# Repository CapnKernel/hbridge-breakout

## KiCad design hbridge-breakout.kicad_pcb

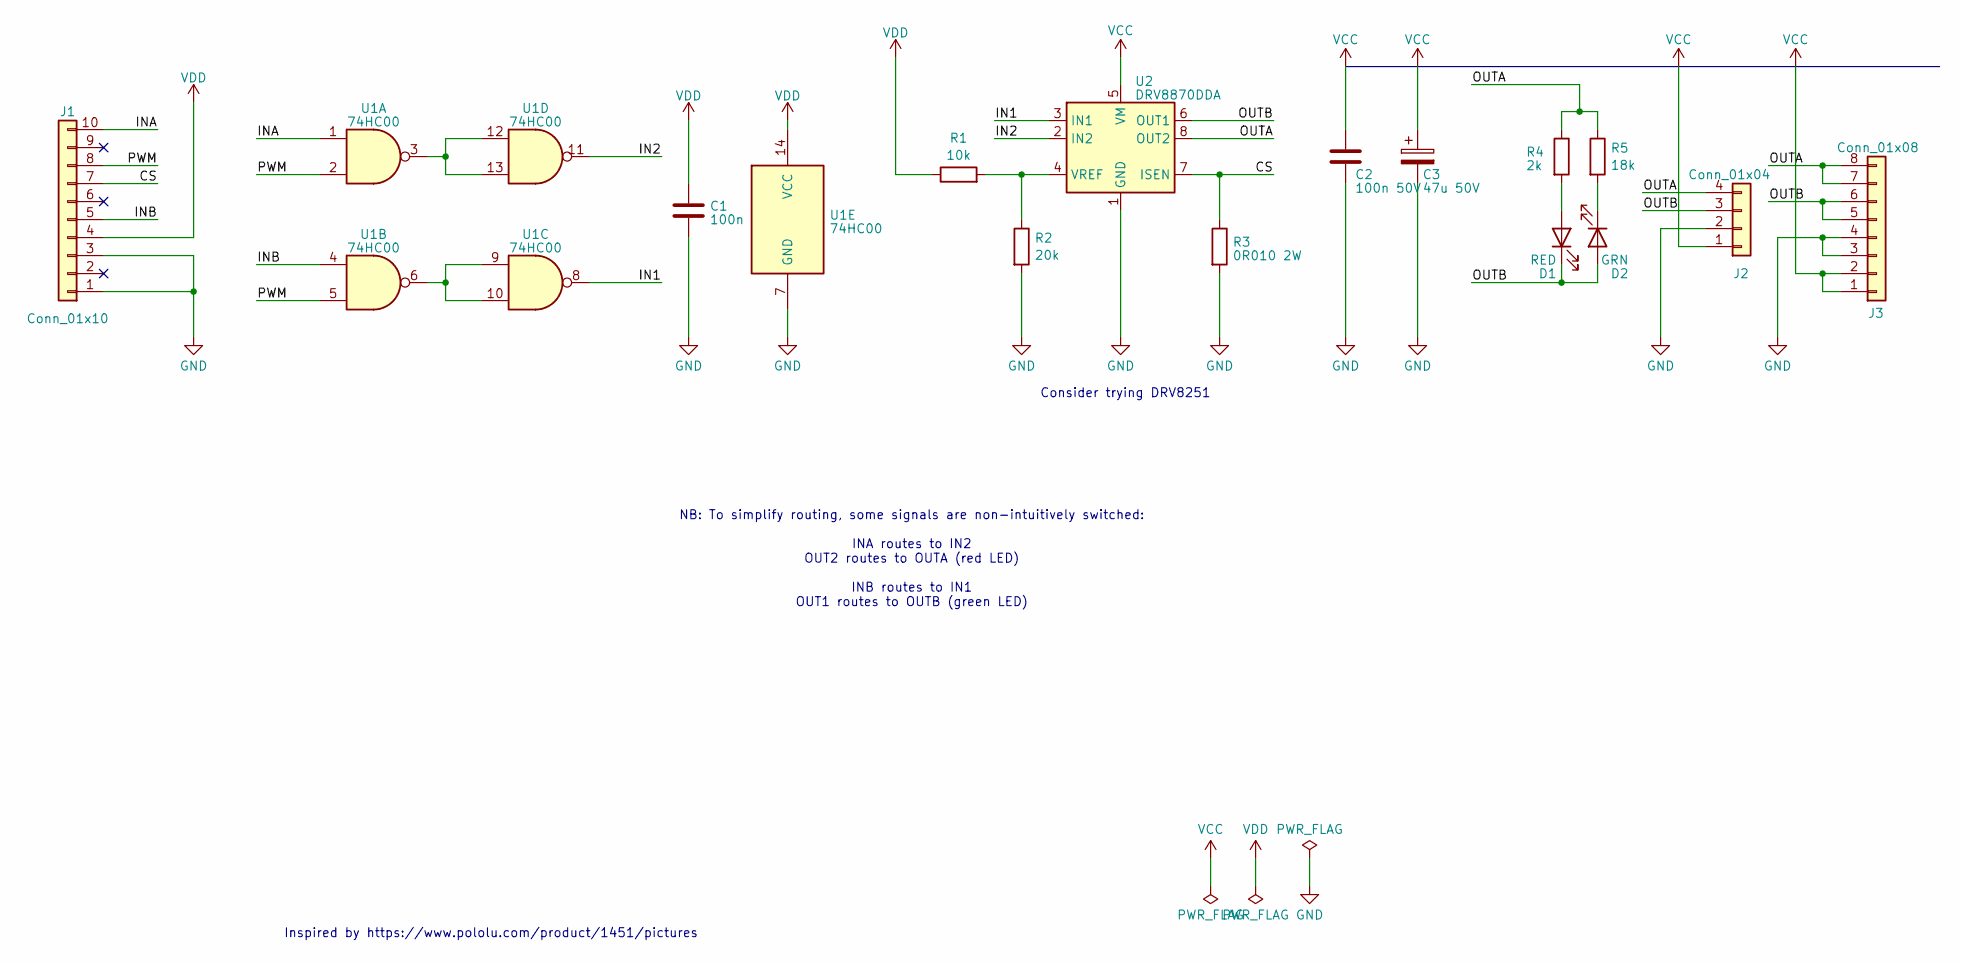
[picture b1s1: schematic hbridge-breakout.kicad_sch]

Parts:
C1: 100n; C_0805_2012Metric_Pad1.18x1.45mm_HandSolder
C2: 100n 50V; C_0805_2012Metric_Pad1.18x1.45mm_HandSolder
C3: 47u 50V; CP_Radial_D6.3mm_P2.50mm
D1: RED; LED_0805_2012Metric_Pad1.15x1.40mm_HandSolder
D2: GRN; LED_0805_2012Metric_Pad1.15x1.40mm_HandSolder
J1: Conn_01x10; PinHeader_1x10_P2.54mm_Vertical
J2: Conn_01x04; PinHeader_1x04_P5.04mm_Vertical
J3: Conn_01x08; PinHeader_1x08_P2.54mm_Vertical
R1: 10k; R_0805_2012Metric_Pad1.20x1.40mm_HandSolder
R2: 20k; R_0805_2012Metric_Pad1.20x1.40mm_HandSolder
R3: 0R010 2W; R_2512_6332Metric_Pad1.40x3.35mm_HandSolder
R4: 2k; R_0805_2012Metric_Pad1.20x1.40mm_HandSolder
R5: 18k; R_0805_2012Metric_Pad1.20x1.40mm_HandSolder
U1: 74HC00; DIP-14_W7.62mm_LongPads
U2: DRV8870DDA; Texas_HTSOP-8-1EP_3.9x4.9mm_P1.27mm_EP2.95x4.9mm_Mask2.4x3.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

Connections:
/CS: J1.7, R3.1, U2.7 (ISEN)
/IN1: U1.8, U2.3 (IN1)
/IN2: U1.11, U2.2 (IN2)
/INA: J1.10, U1.1
/INB: J1.5, U1.4
/OUTA: J2.4, J3.7, J3.8, R4.1, R5.1, U2.8 (OUT2)
/OUTB: D1.1 (K), D2.2 (A), J2.3, J3.5, J3.6, U2.6 (OUT1)
/PWM: J1.8, U1.2, U1.5
GND: C1.2, C2.2, C3.2, J1.1, J1.3, J2.2, J3.3, J3.4, R2.2, R3.2, U1.7 (GND), U2.1 (GND), U2.9 (GND)
unnamed: D1.2 (A), R4.2
unnamed: D2.1 (K), R5.2
unnamed: U1.6, U1.9, U1.10
unnamed: U1.3, U1.12, U1.13
unnamed: R1.2, R2.1, U2.4 (VREF)
VCC: C2.1, C3.1, J2.1, J3.1, J3.2, U2.5 (VM)
VDD: C1.1, J1.4, R1.1, U1.14 (VCC)

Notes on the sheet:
NB: To simplify routing, some signals are non-intuitively switched: INA routes to IN2 OUT2 routes to OUTA (red LED) INB routes to IN1 OUT1 routes to OUTB (green LED)
Consider trying DRV8251
Inspired by https://www.pololu.com/product/1451/pictures

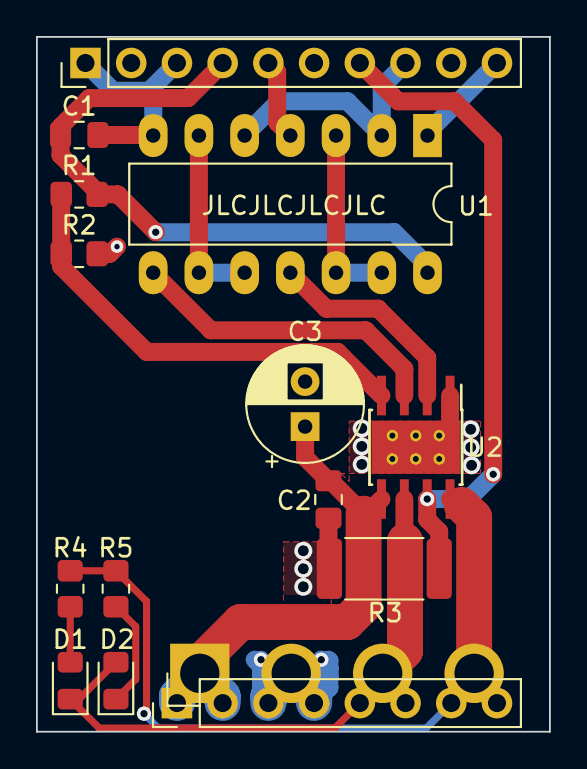
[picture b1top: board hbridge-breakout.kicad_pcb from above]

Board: 2 copper layers, 28.5 x 38.6 mm, 15 parts (0 on the bottom side), 16 nets.

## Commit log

2023-05-10 v1.0a
2023-05-10 Added JLCJLCJLCJLC
2023-05-23 Moved current sense via away from chip pin pad, thickened trace.
2023-08-16 Hide 3d models of power/motor headers
2023-08-16 Improved CS trace to not cut the ground plane so much.
2023-08-16 Each direction LED now has its own dropper resistor.
2023-08-16 Added labels to pins
2023-09-19 Add note to try DRV8251
2023-09-19 Heap of rework to make power tracks simpler, and caps closer to chip.
2024-04-18 Update for KiCad 8
2024-04-18 Fixed a terrible bug where the power input/outputs at the bottom of the board were flipped.
